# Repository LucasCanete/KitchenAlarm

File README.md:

# KitchenAlarm
A small Atmega168 based Kitchentimer to measure cooking time for your meals. Forget about downloading another app or using your phone. Do it the old fashioned way, like  it's the 90's. Put the pizza in the oven, configure your Kitchenalarm and let it beep like a fire alarm on steroids when your pizza is ready.

## Table of Contents
1. [About the Project](#about-the-project)
2. [Features](#features)
3. [Components](#components)
4. [Getting Started](#getting-started)
5. [Project Status](#project-status)

## About the project
This one was one of my first projects writing bare metal C. What i wanted to do is develop the simplest device possible, write the software, make a pcb and print a 3D case for it. A Timer is a device everyone is familiar with, so i decided to go for that. I took an atmega168, programmed it using avrdude and made a simple pcb for the circuitry using KiCad. Using the OnShape software i designed a case for the pcb and this was the end result.

## Features
- Rotary Encoder for configuring minutes and seconds
- 4 Digit 7 Segment Display for displaying the time
- Buzzer Alarm for beeping when time has runned up
- Deep sleep Mode after 1 Minute of not receiving instructions

## Components
| Component | Model  | Manufacturer  |
|:--------|:------:|------:|
| Microcontroller  | atmega168 | Microchip |
| 7 Seg. Display  | Generic | - |
| Rotary Encoder Module  | KY-040 | - |
| Battery Charger  | BQ24090 | Texas Instruments |

## Getting Started
### Install AVRDUDE
```
sudo apt install avrdude
```
### Download this repo
```
git clone https://github.com/LucasCanete/KitchenAlarm.git
```
### Build and upload 
Connect the KitchenAlarm to the PC using usbasp and upload the code:
```
cd KitchenAlarm/Software
$KitchenAlarm/Software make
$KitchenAlarm/Software make flash
```
### Use
The Kitchenalarm has a **Rotary Encoder** that lets you configure the Minutes and Seconds through the encoder's rotation.
1. Press the Rotary Encoder on the board to configure the Minutes and adjust it rotating the encoder 
2. Press it once again to configure the Seconds and rotate it to adjust 
3. Press the encoder one last time to activate the Timer with the Minutes and Seconds you configured in step 1 and step 2. The Timer will start counting down on the 7-Segment Display (To reset the countdown press the Encoder)
4. When the Timer reaches 00:00 (on the Display) the buzzer on the Board will start beeping. Your pizza is ready. Press the Encoder once to stop the beeping
5. The Kitchenalarm goes automatically to deep sleep if it is not given instructions. To wake it up just press the Encoder

## Project Status
This project is currently on stand by. After three iterations and continuous improvement i decided to pause the project. I have learn a lot: pcb design, embedded programming, 3d printing, etc. but now i want to focus on other projects.
The main issue with this project right now is the battery charger with the BQ24090 Chip. With the current design the charger is unable to detect the battery load and fully charge it. I do not have the patience at the moment to find out what the issue is. In the future when i posses more knowledge i will resume with this project.

Some ideas i have for the project are:

- [x] Use LED driver chip (e.g. MAX7219) for driving the 7 segment display (Spares me a lot of gpios)
- [x] Add a quartz crystal to the atmega for more precise counting
      
These new features have already been implemented in the new KiCad design and can be seen in the **Hardware** directory. Once i solder the new pcb i will upload the results with pictures.

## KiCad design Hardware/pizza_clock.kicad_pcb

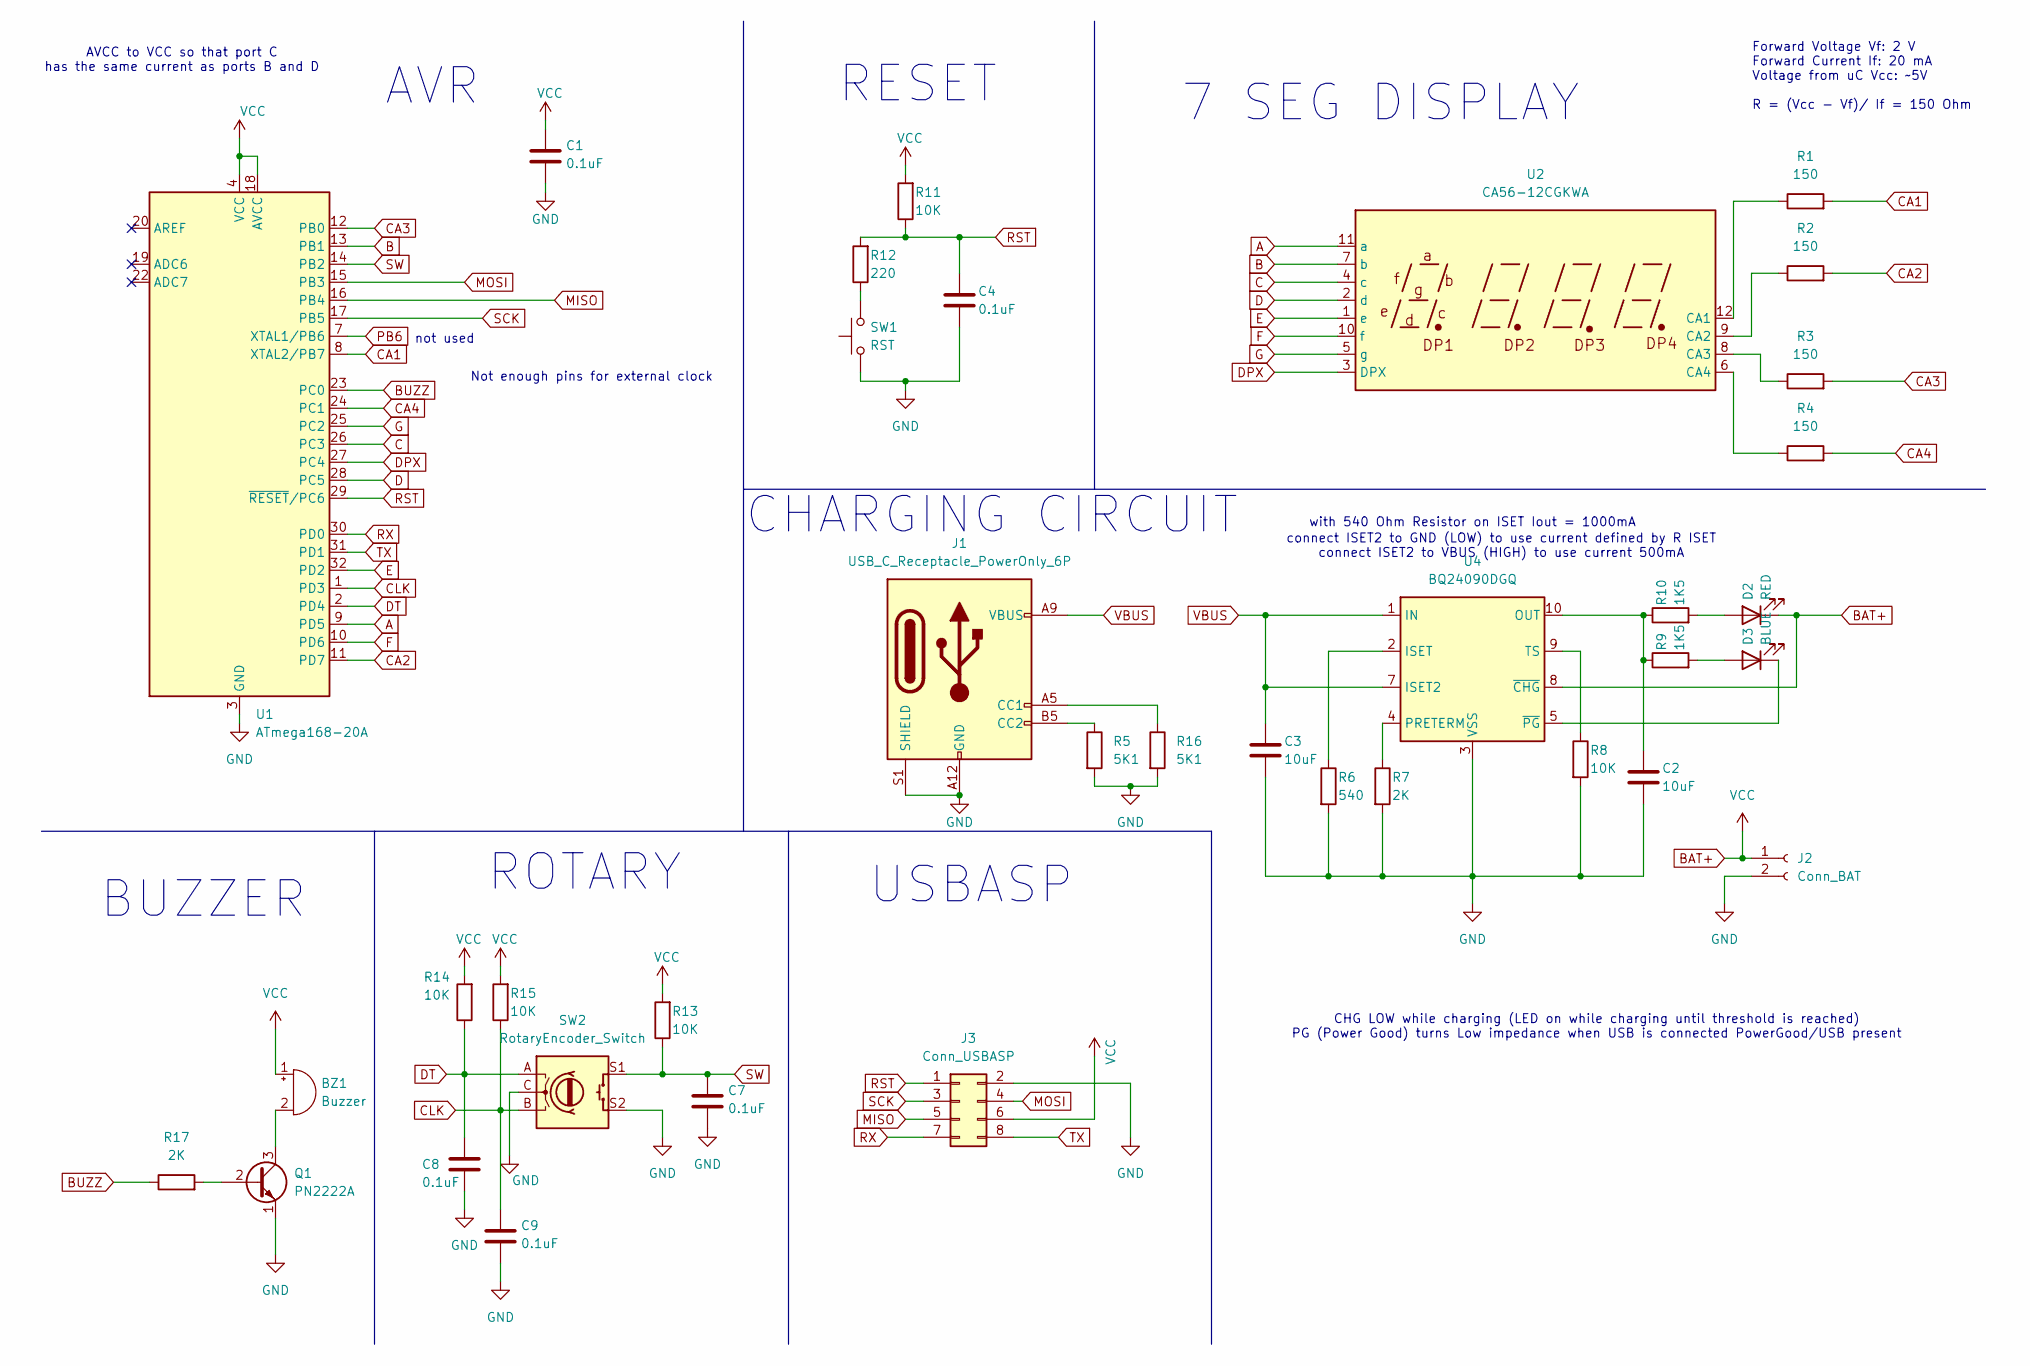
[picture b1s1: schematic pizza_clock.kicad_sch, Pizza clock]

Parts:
BZ1: Buzzer; Buzzer_12x9.5RM7.6
C1, C4, C7, C8, C9: 0.1uF; C_1206_3216Metric_Pad1.33x1.80mm_HandSolder
C2, C3: 10uF; C_1206_3216Metric_Pad1.33x1.80mm_HandSolder
D2: RED; LED_0805_2012Metric
D3: BLUE; LED_0805_2012Metric
J1: USB_C_Receptacle_PowerOnly_6P; USB_C_Receptacle_GCT_USB4135-GF-A_6P_TopMnt_Horizontal
J2: Conn_BAT; JST_GH_SM02B-GHS-TB_1x02-1MP_P1.25mm_Horizontal
J3: Conn_USBASP; PinSocket_2x04_P2.54mm_Vertical
Q1: PN2222A; TO-92_Inline
R1, R2, R3, R4: 150; R_1206_3216Metric_Pad1.30x1.75mm_HandSolder
R5, R16: 5K1; R_1206_3216Metric_Pad1.30x1.75mm_HandSolder
R6: 540; R_1206_3216Metric_Pad1.30x1.75mm_HandSolder
R7, R17: 2K; R_1206_3216Metric_Pad1.30x1.75mm_HandSolder
R8, R11, R13, R14, R15: 10K; R_1206_3216Metric_Pad1.30x1.75mm_HandSolder
R9, R10: 1K5; R_1206_3216Metric_Pad1.30x1.75mm_HandSolder
R12: 220; R_1206_3216Metric_Pad1.30x1.75mm_HandSolder
SW1: RST; SW_Tactile_SPST_NO_Straight_CK_PTS636Sx25SMTRLFS
SW2: RotaryEncoder_Switch; RotaryEncoder_Alps_EC11E-Switch_Vertical_H20mm
U1: ATmega168-20A; TQFP-32_7x7mm_P0.8mm
U2: CA56-12CGKWA
U4: BQ24090DGQ; HVSSOP-10-1EP_3x3mm_P0.5mm_EP1.57x1.88mm_ThermalVias

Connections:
A: U1.9 (PD5), U2.11 (a)
B: U1.13 (PB1), U2.7 (b)
BAT+: BZ1.1 (-), C1.1, D2.1 (K), J2.1, J3.6, R11.2, R13.2, R14.2, R15.2, U1.4 (VCC), U1.6 (VCC), U1.18 (AVCC), U4.8 (~CHG)
BUZZ: R17.1, U1.23 (PC0)
C: U1.26 (PC3), U2.4 (c)
CA1: R1.2, U1.8 (XTAL2/PB7)
CA2: R2.2, U1.11 (PD7)
CA3: R3.2, U1.12 (PB0)
CA4: R4.2, U1.24 (PC1)
CLK: C9.1, R15.1, SW2.B, U1.1 (PD3)
D: U1.28 (PC5), U2.2 (d)
DPX: U1.27 (PC4), U2.3 (DPX)
DT: C8.1, R14.1, SW2.A, U1.2 (PD4)
E: U1.32 (PD2), U2.1 (e)
F: U1.10 (PD6), U2.10 (f)
G: U1.25 (PC2), U2.5 (g)
GND: C1.2, C2.2, C3.2, C4.2, C7.2, C8.2, C9.2, J1.A12 (GND), J1.B12 (GND), J1.S1 (SHIELD), J2.2, J3.2, Q1.1 (E), R5.2, R6.2, R7.2, R8.2, R16.2, SW1.1, SW2.C, SW2.S2, U1.3 (GND), U1.5 (GND), U1.21 (GND), U4.3 (VSS), U4.11 (VSS)
MISO: J3.5, U1.16 (PB4)
MOSI: J3.4, U1.15 (PB3)
unnamed: BZ1.2 (+), Q1.3 (C)
unnamed: D2.2 (A), R10.2
unnamed: D3.2 (A), R9.2
unnamed: D3.1 (K), U4.5 (~PG)
unnamed: J1.A5 (CC1), R16.1
unnamed: J1.B5 (CC2), R5.1
unnamed: Q1.2 (B), R17.2
unnamed: R12.1, SW1.2
unnamed: R1.1, U2.12 (CA1)
unnamed: R2.1, U2.9 (CA2)
unnamed: R3.1, U2.8 (CA3)
unnamed: R4.1, U2.6 (CA4)
unnamed: R6.1, U4.2 (ISET)
unnamed: C2.1, R9.1, R10.1, U4.10 (OUT)
unnamed: R7.1, U4.4 (PRETERM)
unnamed: R8.1, U4.9 (TS)
PB6: U1.7 (XTAL1/PB6)
RST: C4.1, J3.1, R11.1, R12.2, U1.29 (~RESET/PC6)
RX: J3.7, U1.30 (PD0)
SCK: J3.3, U1.17 (PB5)
SW: C7.1, R13.1, SW2.S1, U1.14 (PB2)
TX: J3.8, U1.31 (PD1)
VBUS: C3.1, J1.A9 (VBUS), J1.B9 (VBUS), U4.1 (IN), U4.7 (ISET2)

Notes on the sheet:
7 SEG DISPLAY
CHG LOW while charging (LED on while charging until threshold is reached) PG (Power Good) turns Low impedance when USB is connected PowerGood/USB present
USBASP
not used
AVCC to VCC so that port C has the same current as ports B and D
AVR
RESET
BUZZER
with 540 Ohm Resistor on ISET Iout = 1000mA
Not enough pins for external clock
Forward Voltage Vf: 2 V Forward Current If: 20 mA Voltage from uC Vcc: ~5V R = (Vcc - Vf)/ If = 150 Ohm
CHARGING CIRCUIT
connect ISET2 to GND (LOW) to use current defined by R ISET connect ISET2 to VBUS (HIGH) to use current 500mA
ROTARY

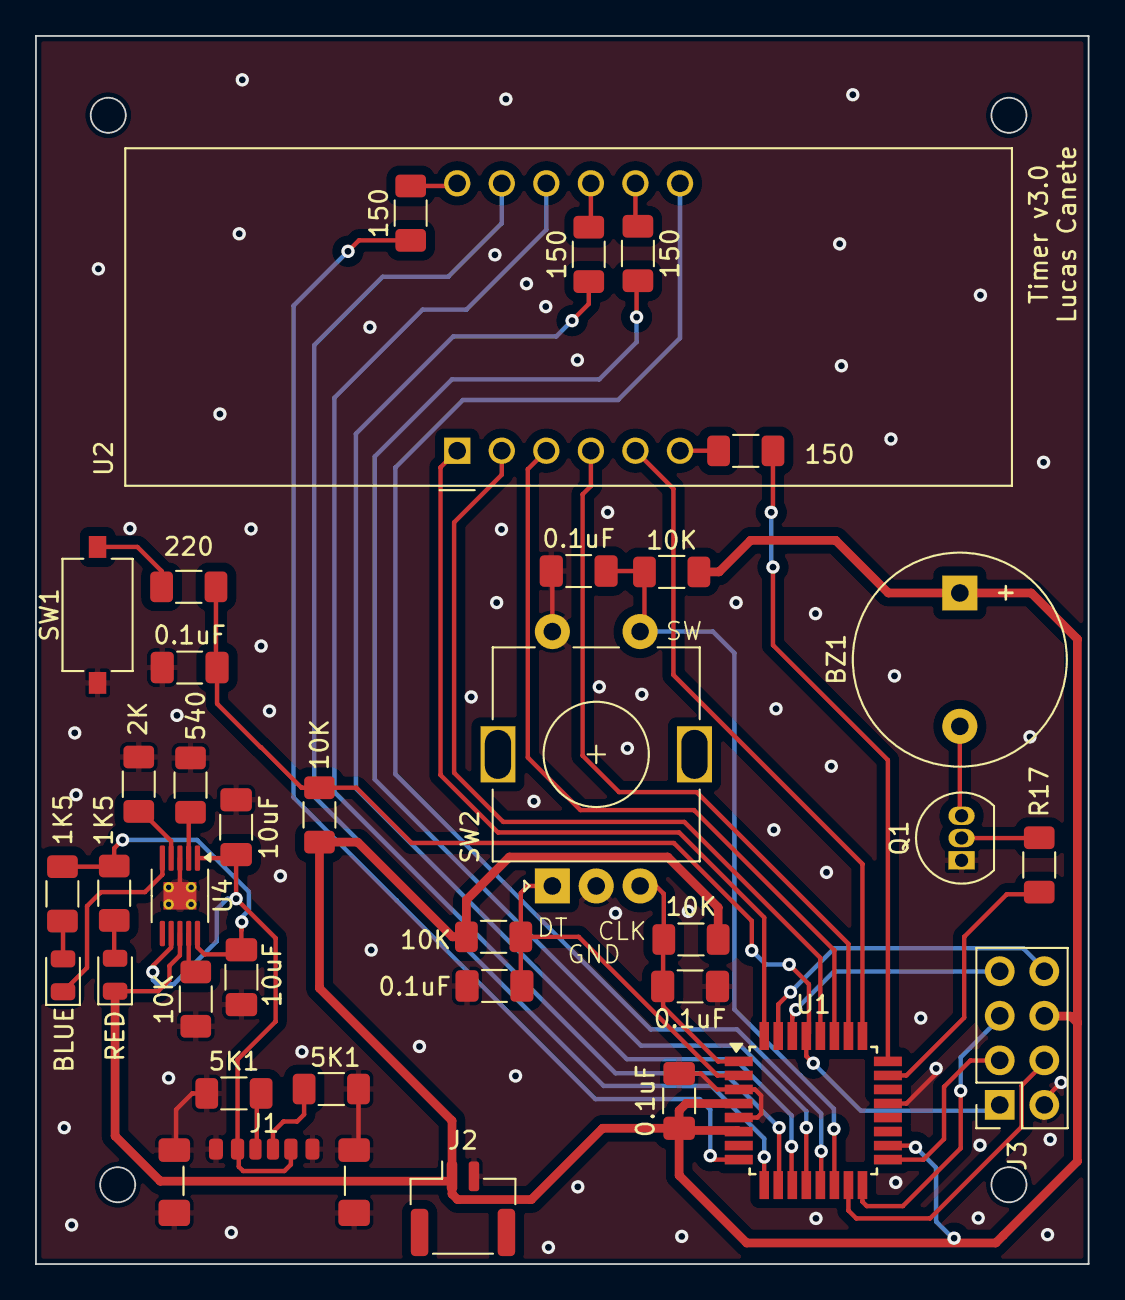
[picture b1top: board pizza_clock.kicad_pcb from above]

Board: 2 copper layers, 60.0 x 70.0 mm, 36 parts (0 on the bottom side), 41 nets.

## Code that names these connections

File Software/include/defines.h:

#ifndef DEFINES_H
#define DEFINES_H

/* 4 DIGIT 7 SEGMENT DISPLAY*/

#define A_PIN     PD5
#define A_PORT    DDRD

#define B_PIN     PB1
#define B_PORT    DDRB

#define C_PIN     PC3
#define C_PORT    DDRC

#define D_PIN     PC5
#define D_PORT    DDRC

#define E_PIN     PD2
#define E_PORT    DDRD

#define F_PIN     PD6
#define F_PORT    DDRD

#define G_PIN     PC2
#define G_PORT    DDRC

#define DPX_PIN   PC4
#define DPX_PORT  DDRC

#define CA1_PIN     PB7
#define CA1_PORT    DDRB

#define CA2_PIN     PD7
#define CA2_PORT    DDRD

#define CA3_PIN     PB0
#define CA3_PORT    DDRB

#define CA4_PIN     PC1
#define CA4_PORT    DDRC

/* BUZZER */

#define BUZZER_PORT PORTC
#define BUZZER_DDR  DDRC
#define BUZZER_PIN  PC0


/* ROTARY ENCODER */

#define DT_DIR DDRD
#define DT_PIN PD4

#define CLK_DIR DDRD
#define CLK_PIN PD3

#define BUTTON_DIR DDRB
#define BUTTON_PIN PB2

#endif

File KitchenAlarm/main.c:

/*
 * KitchenAlarm.c
 *
 * Created: 7/8/2022 21:58:45
 * Author : Lucas
 */ 

/*
	AVR		SevSeg Display
	PB0		A
	PB1		B
	PB2		C
	PB3		D
	PB4		E
	PB5		F	
	PB6		G
	
	
	Seven Segment layout:
	--A--
	F	B
	F	B
	--G--
	E	C
	E	C
	--D--
	
*/
#include <avr/io.h>
#include <avr/interrupt.h>
#include <avr/sleep.h>
#include <util/delay.h>
#include <stdbool.h>
#include <stdio.h>

#include <gpio.h>
#include <SevSeg.h>
#include <Buzzer.h>
#include <USART.h>

typedef enum {IDLE, PROG_MIN, PROG_SEC, COUNTDOWN, BEEP} state_t;

state_t state = IDLE;
state_t prev_state = BEEP;
typedef enum {NONE,CLOCKWISE, COUNTERCLOCKWISE} rotary_dir_t;


volatile bool beep_activated = false;
volatile bool was_sleeping = false;
volatile uint16_t COUNTER_TIMEOUT = 0;
bool alarm_is_set = false;
#define SW PD5
#define DT PD6
#define CLK PD7

int8_t unit_sec = 0;
int8_t ten_sec = 0;
	
int8_t unit_min = 0;
int8_t ten_min = 0;



void beep_and_blink(){
	setBit(PORTD,PD2);
	buzzer_peep(&PORTC,PC5);
	_delay_ms(200);
	clearBit(PORTD,PD2);
	buzzer_stop(&PORTC,PC5);
	_delay_ms(200);
}




void display_minutes(){
	clearBit(PORTC,PC0);//setBit(PORTC,PC0);
	SevSeg_display_digit(&PORTB,ten_min);
	_delay_ms(1);
	SevSeg_clear(&PORTB);
	setBit(PORTC,PC0);//clearBit(PORTC,PC0);

	clearBit(PORTC,PC1);//setBit(PORTC,PC1);
	setBit(PORTC,PC4);// activate decimal point
	SevSeg_display_digit(&PORTB,unit_min);
	_delay_ms(1);
	SevSeg_clear(&PORTB);
	clearBit(PORTC,PC4);// deactivate decimal point
	setBit(PORTC,PC1);//clearBit(PORTC,PC1);
}


void display_seconds(){
	clearBit(PORTC,PC2);
	SevSeg_display_digit(&PORTB,ten_sec);
	_delay_ms(1);
	SevSeg_clear(&PORTB);
	setBit(PORTC,PC2);

	clearBit(PORTC,PC3);
	SevSeg_display_digit(&PORTB,unit_sec);
	_delay_ms(1);
	SevSeg_clear(&PORTB);
	setBit(PORTC,PC3);
}

/**
 * @brief Construct a new ISR object
 * 
 * Counts to one minute if it is in IDLE sleep
 * if alarm activavated then decrease counter
 */

ISR(TIMER1_COMPA_vect){
	
		COUNTER_TIMEOUT++;
		if(alarm_is_set && (unit_min + ten_min + unit_sec+ten_sec > 0)) unit_sec--;
		 else if(COUNTER_TIMEOUT == 60 && !alarm_is_set && state == IDLE  ){
	
			SevSeg_clear(&PORTB);
			clearBit(PORTC,PC4); //deactivate decimal point
			COUNTER_TIMEOUT = 0;
			was_sleeping = true;
			
			set_sleep_mode(SLEEP_MODE_PWR_DOWN);   // Set power-down sleep mode
			cli(); //cli before sleep enable to avoid interferance with interrupts
			sleep_enable();   // Enable sleep mode
			sei();
			sleep_cpu();
		
		}

};

/**
 * @brief 
 * State Handler function 
 * Dependent on switch button
 */
volatile uint8_t prevButtonVal = 1; //default state HIGH because of PULLUP RESISTOR
ISR(PCINT2_vect ) {
	//wake uC up
	printString("waking up!!! \r\n");

	uint8_t currentButtonVal = gpioReadPin(&PIND,SW);
	//Falling Edge
	if(prevButtonVal && !currentButtonVal){
		switch(state){

			case IDLE:
				if(!was_sleeping){
					prev_state = IDLE;
					state = PROG_MIN;
				}
				break;
			case PROG_MIN:
				prev_state = PROG_MIN;
				state = PROG_SEC;
				break;
			case PROG_SEC:
				alarm_is_set = true;
				prev_state = PROG_SEC;
				state = COUNTDOWN;
				break;
			case COUNTDOWN:
				COUNTER_TIMEOUT = 0;
				alarm_is_set = false;
				prev_state = COUNTDOWN;
				state = IDLE;
				break;

			case BEEP:
				prev_state = BEEP;
				state = IDLE;
				break;
		}
	}

	prevButtonVal = currentButtonVal;

}

/**
 * @brief 
 * 
 * @param minute_unit 
 * the unit part of the minute
 * @param minute_ten 
 * the tenth part of the minute
 */

void UpDownCounterMinute(int8_t *minute_unit, int8_t *minute_ten){

	if(*minute_unit > 9 && *minute_ten != 5) {
		(*minute_ten)++;
		*minute_unit = 0;
	}
	else if (*minute_unit < 0){
		(*minute_ten)--;
		*minute_unit = 9;
		
	}
	if(*minute_ten == 5 && *minute_unit > 9){
		*minute_ten = 0;
		*minute_unit = 0;
	}
	else if (*minute_ten < 0){
		*minute_ten = 5;
		*minute_unit = 9;
	}
	
};


/**
 * @brief 
 * 
 * @param sec_unit 
 * the ones
 * @param sec_ten 
 * the tens
 * @param min_unit 
 * to bind it to the minutes variable
 */
void UpDownCounterSecond(int8_t *sec_unit, int8_t *sec_ten, int8_t *min_unit ){


	 if(*sec_unit > 9 && *sec_ten != 5) {
		(*sec_ten)++;
		*sec_unit = 0;
	}
	else if (*sec_unit < 0){
		(*sec_ten)--;
		*sec_unit = 9;
		
	}
	
	if(*sec_ten == 5 && *sec_unit > 9){
			(*min_unit)++;
			*sec_ten = 0;
			*sec_unit = 0;
	}
	
	 else if (*sec_ten < 0){
			(*min_unit)--;
			*sec_ten = 5;
			*sec_unit = 9;
	}
	
	
};


void alarm_countdown(int8_t *ten_min, int8_t *unit_min, int8_t *ten_sec, int8_t *unit_sec){
	
			clearBit(PORTC,PC2);
			SevSeg_display_digit(&PORTB,*ten_sec);
			_delay_ms(1);
			SevSeg_clear(&PORTB);
			setBit(PORTC,PC2);
			
			clearBit(PORTC,PC3);
			SevSeg_display_digit(&PORTB,*unit_sec);
			_delay_ms(1);
			SevSeg_clear(&PORTB);
			setBit(PORTC,PC3);
			
			clearBit(PORTC,PC0);
			SevSeg_display_digit(&PORTB,*ten_min);
			_delay_ms(1);
			SevSeg_clear(&PORTB);
			setBit(PORTC,PC0);
			
			clearBit(PORTC,PC1);
			setBit(PORTC,PC4);// activate decimal point
			SevSeg_display_digit(&PORTB,*unit_min);
			_delay_ms(1);
			SevSeg_clear(&PORTB);
			clearBit(PORTC,PC4);// deactivate decimal point
			setBit(PORTC,PC1);
	
}


//returns if rotary is rotating clockwise 1 or counterclockwise 0
uint8_t rotaryEncoderdirection(uint8_t *current_clkstate, uint8_t *last_clkstate){
	uint8_t dir = 3;
	//rotary_dir_t dir = NONE;
	if(*current_clkstate != *last_clkstate && *current_clkstate == 0){
		uint8_t dt_state = bit_is_set(PIND,DT);
		if(dt_state != *current_clkstate){//clockwise

				dir = CLOCKWISE;
			} 
		else if(dt_state == *current_clkstate){//counterclockwise

				dir = COUNTERCLOCKWISE;
			} 
		
	}
	*last_clkstate = *current_clkstate;

	return dir;
}


void initTimer_16bit(){
	
	TCCR1B |= (1<<WGM12); //set CTC mode CAPTURE COMPARE
	OCR1A |= 976;
	TIMSK1 |= (1<<OCIE1A); //enable interrupt
	//timer every 0.01 seconds. For one minute it has to reache 6000 the ISR.	
	sei(); //enable global interrupts
	TCCR1B |= (1<<CS12) | (1<<CS10); //set prescaler (CPU clock)/1024, CPUCLOCK by default = 1MHz
	
}

int main(void)
{
	//init external Interrupt on SW
	PCICR |= (1<< PCIE2); //any change in any pin in portd will activate interrupt
	PCMSK2 |= (1 << SW); //here it is specified which pin from portd will activate interrupt
	
	initTimer_16bit(); //every second
	
	initUSART();

	//disable Analog Comparator
	ACSR |= (1<<ACD);

	//turn off ADC
	ADCSRA &= ~(1<<ADEN);
	
	uint8_t currentStateClk;
	uint8_t lastStateClk;
	uint8_t rotary_direction;
		
	
    for(uint8_t i = 0; i<7; i++){
		setBit(DDRB,i);
	}
	setBit(DDRC,PC0); //ten minute
	setBit(DDRC,PC1); //unit minute
	
	setBit(DDRC,PC2); //ten second
	setBit(DDRC,PC3); //unit second
	
	setBit(DDRC,PC4); //decimal point
	setBit(PORTC,PC4);//deactivate decimal point
	
	setBit(DDRC,PC5); //buzzer
	
	setBit(DDRD,PD2); //alarm led
	
	
	clearBit(DDRD,DT); //input
	clearBit(DDRD,CLK); //input
	clearBit(DDRD,SW); //switch if pressed a 0 is read
	
	lastStateClk = bit_is_set(PIND,CLK); //return non zero if bit is clear. 0 if bit is set


	

    while (1) 
    {

		switch(state){
			case IDLE:
				if(state != prev_state || was_sleeping){
					was_sleeping = 0;
					unit_sec = 0;
					unit_min = 0;
					ten_sec = 0;
					ten_min = 0;
					_delay_ms(500);
					prev_state = state;
				}
				display_seconds();
				display_minutes();

				break;


			case PROG_MIN:
				if(state != prev_state){
					_delay_ms(500);
					prev_state = state;
				}
				display_minutes();

				currentStateClk = bit_is_set(PIND,CLK);
				rotary_direction = rotaryEncoderdirection(&currentStateClk,&lastStateClk);
				if(rotary_direction == CLOCKWISE ){
					unit_min++;
					UpDownCounterMinute(&unit_min, &ten_min);
					}

				else if(rotary_direction == COUNTERCLOCKWISE){
					unit_min--;
					UpDownCounterMinute(&unit_min, &ten_min);
					}

				break;


			case PROG_SEC:
				if(state != prev_state){
					_delay_ms(500);
					prev_state = state;
				}

				display_seconds();

				currentStateClk = bit_is_set(PIND,CLK);
				rotary_direction = rotaryEncoderdirection(&currentStateClk,&lastStateClk);
				if(rotary_direction == CLOCKWISE){
					unit_sec++;
					UpDownCounterMinute(&unit_sec, &ten_sec);
				}
				else if(rotary_direction == COUNTERCLOCKWISE){
					unit_sec--;
					UpDownCounterMinute(&unit_sec, &ten_sec);
				}

				break;


			case COUNTDOWN:
				if(state != prev_state){
					_delay_ms(500);
					prev_state = state;
				}

				alarm_countdown(&ten_min,&unit_min,&ten_sec,&unit_sec); //keep here always before updowncountersecond function
				UpDownCounterSecond(&unit_sec, &ten_sec,&unit_min);
				UpDownCounterMinute(&unit_min, &ten_min);

				if((ten_min + unit_min + ten_sec + unit_sec) == 0 ) {
					COUNTER_TIMEOUT = 0;
					alarm_is_set = false;
					state = BEEP;}

				break;


			case BEEP:
				if(state != prev_state){
					_delay_ms(500);
					prev_state = state;
				}
				beep_and_blink();

				break;

		}

	} //while super loop
	
} //main

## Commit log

2023-12-30 Actualizar README.md
2024-10-28 Update main.c
    Disabled analog comparator and turned off ADC
2025-02-22 Update and rename main.c to main.c
    updated project structure
2025-02-22 Uploaded KiCad files
2025-02-22 Added files to Hardware Directory
2025-08-24 Change C to CPP
